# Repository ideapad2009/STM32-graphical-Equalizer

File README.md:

# STM32-graphical-Equalizer
## STM32F413CG real-time graphical Equalizer using Mems Microphone & DFSDM for Audio Acquisition, I2S & WM8731 codec

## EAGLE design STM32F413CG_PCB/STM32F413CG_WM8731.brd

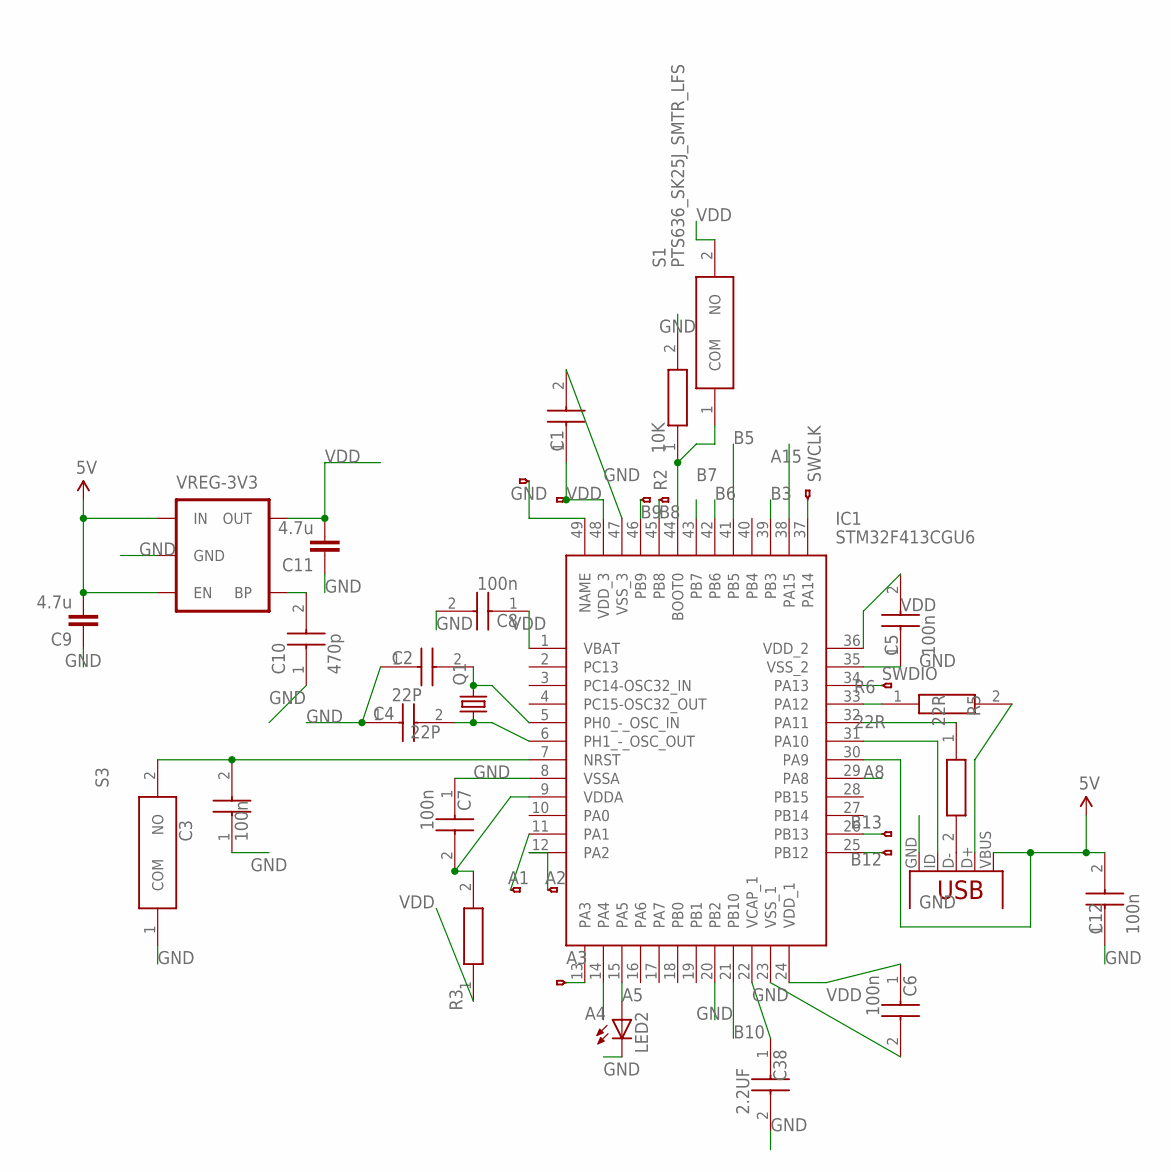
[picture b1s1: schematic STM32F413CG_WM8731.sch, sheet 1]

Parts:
C1: C0603C104M4RAC7411; CAPC1608X95N
C2, C4: 22P; CAPC1608X80N
C3, C5, C6, C7, C8, C12: 100n; CAPC1608X95N
C9, C11: 4.7u; C2.5-3
C10: 470p; CAPC1608X87N
C38: 2.2UF; CAPC2012X145N
IC1: STM32F413CGU6; QFN50P700X700X60-49N
JP1, JP2, JP3, JP4, JP5, JP6, JP7, JP8, JP9, JP10, JP11: HEADERHOLE-HEADERHOLE; 1X1-HEADER-HOLE
LED2: LED0603; LED-0603
Q1: CRYSTALHC49S; HC49/S
R2: 10K; RESC1005X40N
R3: CRCW040222R0FKED; RESC1005X40N
R5, R6: 22R; RESC1005X40N
S1, S3: PTS636_SK25J_SMTR_LFS; PTS636SK25JSMTRLFS
VREG-3V3: V_REG_LDOSMD; SOT23-5
X1: USB-MICROB-SMD

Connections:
5V: C9.2, C12.2, IC1.30 (PA9), VREG-3V3.1 (IN), VREG-3V3.3 (EN), X1.VBUS
A1: IC1.11 (PA1), JP8.1
A2: IC1.12 (PA2), JP9.1
A3: IC1.13 (PA3), JP10.1
A4: IC1.14 (PA4); also elsewhere on the board
A5: IC1.15 (PA5), LED2.A
A8: IC1.29 (PA8); also elsewhere on the board
A15: IC1.38 (PA15); also elsewhere on the board
B3: IC1.39 (PB3); also elsewhere on the board
B5: IC1.41 (PB5); also elsewhere on the board
B6: IC1.42 (PB6); also elsewhere on the board
B7: IC1.43 (PB7); also elsewhere on the board
B8: IC1.45 (PB8), JP5.1
B9: IC1.46 (PB9), JP11.1
B10: IC1.21 (PB10); also elsewhere on the board
B12: IC1.25 (PB12), JP7.1
B13: IC1.26 (PB13), JP6.1
GND: C1.2, C2.1, C3.1, C4.1, C5.1, C6.2, C7.1, C8.2, C9.1, C10.1, C11.1, C12.1, C38.2, IC1.8 (VSSA), IC1.20 (PB2), IC1.23 (VSS_1), IC1.35 (VSS_2), IC1.47 (VSS_3), IC1.49 (NAME), JP1.1, LED2.C, R2.2, S3.1 (COM), VREG-3V3.2 (GND), X1.GND; also elsewhere on the board
unnamed: C2.2, IC1.5 (PH0_-_OSC_IN), Q1.2
unnamed: C3.2, IC1.7 (NRST), S3.2 (NO)
unnamed: C10.2, VREG-3V3.4 (BP)
unnamed: C7.2, IC1.9 (VDDA), R3.2
unnamed: R5.2, X1.D-
unnamed: IC1.31 (PA10), X1.ID
unnamed: IC1.32 (PA11), R5.1
unnamed: R6.2, X1.D+
unnamed: IC1.33 (PA12), R6.1
unnamed: IC1.44 (BOOT0), R2.1, S1.1 (COM)
unnamed: C4.2, IC1.6 (PH1_-_OSC_OUT), Q1.1
unnamed: C38.1, IC1.22 (VCAP_1)
SWCLK: IC1.37 (PA14), JP2.1
SWDIO: IC1.34 (PA13), JP3.1
VDD: C1.1, C5.2, C6.1, C8.1, C11.2, IC1.1 (VBAT), IC1.24 (VDD_1), IC1.36 (VDD_2), IC1.48 (VDD_3), JP4.1, R3.1, S1.2 (NO), VREG-3V3.5 (OUT); also elsewhere on the board

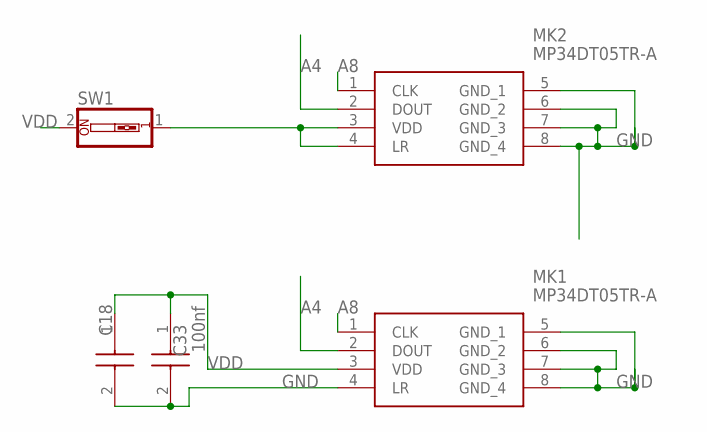
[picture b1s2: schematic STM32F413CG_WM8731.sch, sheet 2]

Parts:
C18: 1UF; CAPC1005X55N
C33: 100nf; CAPC1608X95N
MK1, MK2: MP34DT05TR-A; MP34DT05TRA
SW1: SW_DIP-1; EDG-01

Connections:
A4: MK1.2 (DOUT), MK2.2 (DOUT); also elsewhere on the board
A8: MK1.1 (CLK), MK2.1 (CLK); also elsewhere on the board
GND: C18.2 (C2), C33.2, MK1.4 (LR), MK1.5 (GND_1), MK1.6 (GND_2), MK1.7 (GND_3), MK1.8 (GND_4), MK2.5 (GND_1), MK2.6 (GND_2), MK2.7 (GND_3), MK2.8 (GND_4); also elsewhere on the board
unnamed: MK2.3 (VDD), MK2.4 (LR), SW1.1
VDD: C18.1 (C1), C33.1, MK1.3 (VDD), SW1.2; also elsewhere on the board

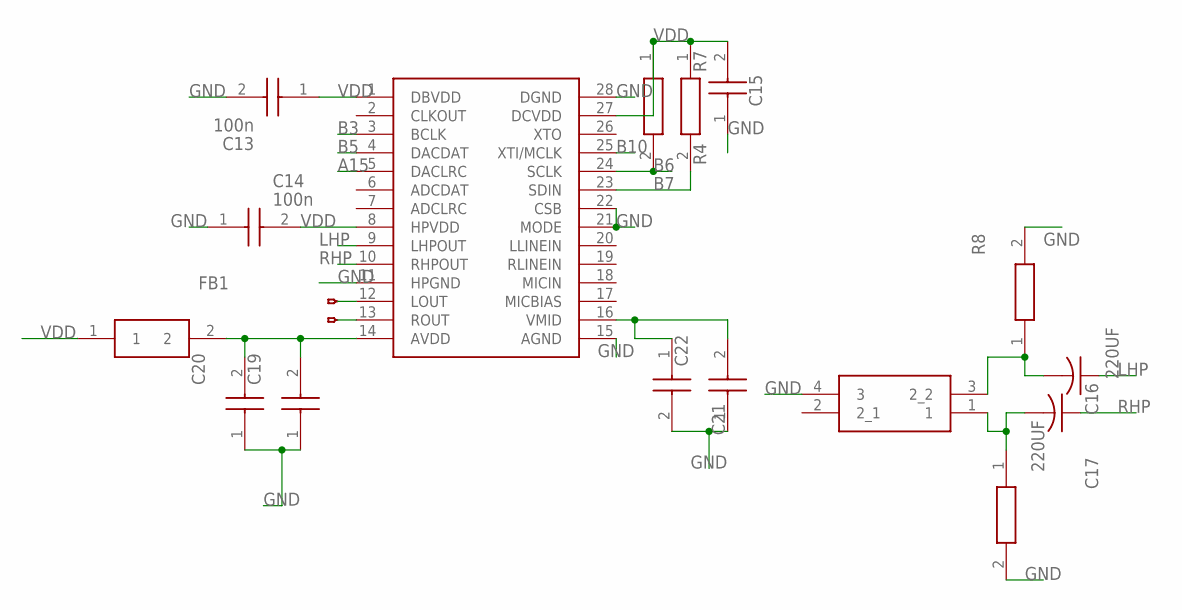
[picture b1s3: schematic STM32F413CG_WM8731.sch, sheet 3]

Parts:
C13, C14: 100n; CAPC1608X95N
C15, C19, C22: C0603C104M4RAC7411; CAPC1608X95N
C16, C17: 220UF; C025-024X044
C20: CL21A106KAYNNNE_10UF; CAPC2012X145N
C21: CL21A106KAYNNNE; CAPC2012X145N
FB1: BLM18BD252SN1D; BEADC1608X95N
IC2: WM8731SEDS_RV; SOP65P780X200-28N
J2: 1503_02; 150302
JP12, JP13: HEADERHOLE-HEADERHOLE; 1X1-HEADER-HOLE
R4, R7, R8, R9: CR0603-JW-472ELF; RESC1608X55N

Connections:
A15: IC2.5 (DACLRC); also elsewhere on the board
B3: IC2.3 (BCLK); also elsewhere on the board
B5: IC2.4 (DACDAT); also elsewhere on the board
B6: IC2.24 (SCLK), R4.2; also elsewhere on the board
B7: IC2.23 (SDIN), R7.2; also elsewhere on the board
B10: IC2.25 (XTI/MCLK); also elsewhere on the board
GND: C13.2, C14.1, C15.1, C19.1, C20.1, C21.2, C22.1, IC2.11 (HPGND), IC2.15 (AGND), IC2.21 (MODE), IC2.22 (CSB), IC2.28 (DGND), J2.4 (3), R8.2, R9.2; also elsewhere on the board
LHP: C16.1, IC2.9 (LHPOUT)
unnamed: C16.2, J2.3 (2_2), R8.1
unnamed: C19.2, C20.2, FB1.2, IC2.14 (AVDD)
unnamed: C21.1, C22.2, IC2.16 (VMID)
unnamed: IC2.12 (LOUT), JP13.1
unnamed: IC2.13 (ROUT), JP12.1
unnamed: C17.2, J2.1, R9.1
RHP: C17.1, IC2.10 (RHPOUT)
VDD: C13.1, C14.2, C15.2, FB1.1, IC2.1 (DBVDD), IC2.8 (HPVDD), IC2.27 (DCVDD), R4.1, R7.1; also elsewhere on the board

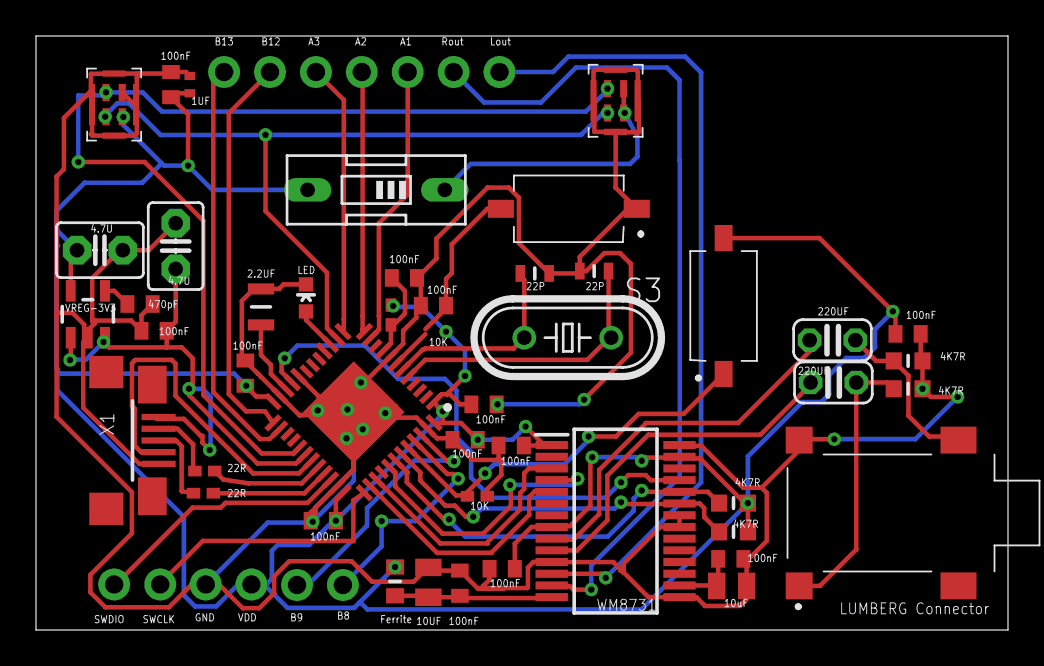
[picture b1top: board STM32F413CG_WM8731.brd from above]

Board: 2 copper layers, 54.0 x 33.0 mm, 58 parts (0 on the bottom side), 42 nets.

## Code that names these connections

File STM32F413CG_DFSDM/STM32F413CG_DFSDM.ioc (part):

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Mcu.Name=STM32F413C(G-H)Ux
Mcu.Package=UFQFPN48
Mcu.UserName=STM32F413CGUx
PA13.Mode=Serial_Wire
PA13.Signal=SYS_JTMS-SWDIO
PA14.Mode=Serial_Wire
PA14.Signal=SYS_JTCK-SWCLK
PA4.Signal=COMP_DAC1_group
PA5.GPIOParameters=GPIO_Speed,PinState
PA5.GPIO_Speed=GPIO_SPEED_FREQ_HIGH
PA5.PinState=GPIO_PIN_SET
PA5.Signal=GPIO_Output
PA8.Signal=S_CKOUTDFSDM1
PB12.Signal=S_DATAIN1DFSDM1
PB3.Signal=I2S3_CK
PB6.Mode=I2C
PB6.Signal=I2C1_SCL
PB7.Mode=I2C
PB7.Signal=I2C1_SDA
PB8.Mode=Asynchronous
PB8.Signal=UART5_RX
PB9.Mode=Asynchronous
PB9.Signal=UART5_TX
PH0\ -\ OSC_IN.Mode=HSE-External-Oscillator
PH0\ -\ OSC_IN.Signal=RCC_OSC_IN
PH1\ -\ OSC_OUT.Mode=HSE-External-Oscillator
PH1\ -\ OSC_OUT.Signal=RCC_OSC_OUT
RCC.HSE_VALUE=8000000
RCC.SYSCLKFreq_VALUE=80000000
RCC.SYSCLKSource=RCC_SYSCLKSOURCE_PLLCLK
board=custom

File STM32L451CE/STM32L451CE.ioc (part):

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Mcu.Name=STM32L451C(C-E)Ux
Mcu.Package=UFQFPN48
Mcu.UserName=STM32L451CEUx
PA10.Mode=Asynchronous
PA10.Signal=USART1_RX
PA13\ (JTMS/SWDIO).Mode=Serial_Wire
PA13\ (JTMS/SWDIO).Signal=SYS_JTMS-SWDIO
PA14\ (JTCK/SWCLK).Mode=Serial_Wire
PA14\ (JTCK/SWCLK).Signal=SYS_JTCK-SWCLK
PA4.Signal=COMP_DAC11_group
PA5.Signal=S_CKOUTDFSDM1
PA7.Signal=S_DATAIN0DFSDM1
PA8.GPIOParameters=PinState
PA8.PinState=GPIO_PIN_SET
PA8.Signal=GPIO_Output
PA9.Mode=Asynchronous
PA9.Signal=USART1_TX
PB6.Mode=I2C
PB6.Signal=I2C1_SCL
PB7.Mode=I2C
PB7.Signal=I2C1_SDA
PB8.Signal=GPIO_Output
RCC.HSE_VALUE=8000000
RCC.SYSCLKFreq_VALUE=72000000
RCC.SYSCLKSource=RCC_SYSCLKSOURCE_PLLCLK
board=custom

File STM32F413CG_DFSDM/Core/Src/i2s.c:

/**
  ******************************************************************************
  * File Name          : I2S.c
  * Description        : This file provides code for the configuration
  *                      of the I2S instances.
  ******************************************************************************
  * @attention
  *
  * <h2><center>&copy; Copyright (c) 2020 STMicroelectronics.
  * All rights reserved.</center></h2>
  *
  * This software component is licensed by ST under BSD 3-Clause license,
  * the "License"; You may not use this file except in compliance with the
  * License. You may obtain a copy of the License at:
  *                        opensource.org/licenses/BSD-3-Clause
  *
  ******************************************************************************
  */

/* Includes ------------------------------------------------------------------*/
#include "i2s.h"

/* USER CODE BEGIN 0 */

/* USER CODE END 0 */

I2S_HandleTypeDef hi2s3;
DMA_HandleTypeDef hdma_spi3_tx;

/* I2S3 init function */
void MX_I2S3_Init(void)
{

  hi2s3.Instance = SPI3;
  hi2s3.Init.Mode = I2S_MODE_MASTER_TX;
  hi2s3.Init.Standard = I2S_STANDARD_PHILIPS;
  hi2s3.Init.DataFormat = I2S_DATAFORMAT_24B;
  hi2s3.Init.MCLKOutput = I2S_MCLKOUTPUT_ENABLE;
  hi2s3.Init.AudioFreq = I2S_AUDIOFREQ_48K;
  hi2s3.Init.CPOL = I2S_CPOL_LOW;
  hi2s3.Init.ClockSource = I2S_CLOCK_PLL;
  hi2s3.Init.FullDuplexMode = I2S_FULLDUPLEXMODE_DISABLE;
  if (HAL_I2S_Init(&hi2s3) != HAL_OK)
  {
    Error_Handler();
  }

}

void HAL_I2S_MspInit(I2S_HandleTypeDef* i2sHandle)
{

  GPIO_InitTypeDef GPIO_InitStruct = {0};
  if(i2sHandle->Instance==SPI3)
  {
  /* USER CODE BEGIN SPI3_MspInit 0 */

  /* USER CODE END SPI3_MspInit 0 */
    /* I2S3 clock enable */
    __HAL_RCC_SPI3_CLK_ENABLE();

    __HAL_RCC_GPIOB_CLK_ENABLE();
    __HAL_RCC_GPIOA_CLK_ENABLE();
    /**I2S3 GPIO Configuration
    PB10     ------> I2S3_MCK
    PA15     ------> I2S3_WS
    PB3     ------> I2S3_CK
    PB5     ------> I2S3_SD
    */
    GPIO_InitStruct.Pin = GPIO_PIN_10|GPIO_PIN_3|GPIO_PIN_5;
    GPIO_InitStruct.Mode = GPIO_MODE_AF_PP;
    GPIO_InitStruct.Pull = GPIO_NOPULL;
    GPIO_InitStruct.Speed = GPIO_SPEED_FREQ_LOW;
    GPIO_InitStruct.Alternate = GPIO_AF6_SPI3;
    HAL_GPIO_Init(GPIOB, &GPIO_InitStruct);

    GPIO_InitStruct.Pin = GPIO_PIN_15;
    GPIO_InitStruct.Mode = GPIO_MODE_AF_PP;
    GPIO_InitStruct.Pull = GPIO_NOPULL;
    GPIO_InitStruct.Speed = GPIO_SPEED_FREQ_LOW;
    GPIO_InitStruct.Alternate = GPIO_AF6_SPI3;
    HAL_GPIO_Init(GPIOA, &GPIO_InitStruct);

    /* I2S3 DMA Init */
    /* SPI3_TX Init */
    hdma_spi3_tx.Instance = DMA1_Stream7;
    hdma_spi3_tx.Init.Channel = DMA_CHANNEL_0;
    hdma_spi3_tx.Init.Direction = DMA_MEMORY_TO_PERIPH;
    hdma_spi3_tx.Init.PeriphInc = DMA_PINC_DISABLE;
    hdma_spi3_tx.Init.MemInc = DMA_MINC_ENABLE;
    hdma_spi3_tx.Init.PeriphDataAlignment = DMA_PDATAALIGN_HALFWORD;
    hdma_spi3_tx.Init.MemDataAlignment = DMA_MDATAALIGN_HALFWORD;
    hdma_spi3_tx.Init.Mode = DMA_CIRCULAR;
    hdma_spi3_tx.Init.Priority = DMA_PRIORITY_HIGH;
    hdma_spi3_tx.Init.FIFOMode = DMA_FIFOMODE_DISABLE;
    if (HAL_DMA_Init(&hdma_spi3_tx) != HAL_OK)
    {
      Error_Handler();
    }

    __HAL_LINKDMA(i2sHandle,hdmatx,hdma_spi3_tx);

  /* USER CODE BEGIN SPI3_MspInit 1 */

  /* USER CODE END SPI3_MspInit 1 */
  }
}

void HAL_I2S_MspDeInit(I2S_HandleTypeDef* i2sHandle)
{

  if(i2sHandle->Instance==SPI3)
  {
  /* USER CODE BEGIN SPI3_MspDeInit 0 */

  /* USER CODE END SPI3_MspDeInit 0 */
    /* Peripheral clock disable */
    __HAL_RCC_SPI3_CLK_DISABLE();

    /**I2S3 GPIO Configuration
    PB10     ------> I2S3_MCK
    PA15     ------> I2S3_WS
    PB3     ------> I2S3_CK
    PB5     ------> I2S3_SD
    */
    HAL_GPIO_DeInit(GPIOB, GPIO_PIN_10|GPIO_PIN_3|GPIO_PIN_5);

    HAL_GPIO_DeInit(GPIOA, GPIO_PIN_15);

    /* I2S3 DMA DeInit */
    HAL_DMA_DeInit(i2sHandle->hdmatx);
  /* USER CODE BEGIN SPI3_MspDeInit 1 */

  /* USER CODE END SPI3_MspDeInit 1 */
  }
}

/* USER CODE BEGIN 1 */

/* USER CODE END 1 */

/************************ (C) COPYRIGHT STMicroelectronics *****END OF FILE****/

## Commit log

2020-04-24 STM32F413CG project
2020-04-24 clear repo
2020-04-25 added graphical equalizer libraray
2020-05-01 added CMSIS
2020-06-11 stable release
2020-06-12 first commit test
2020-06-12 continue master
2020-06-12 changed DFSDM MIC polarity
2020-06-12 testtt
2020-06-12 changed sampling frequency of DFSDM and I2S to 44642
2020-06-12 fixed DFDDM MUX to change sampling frequency of DFSDM and I2S to 44642
2020-07-18 Successfully test DAC with Timer6
2020-07-25 test to DAC_output branch
2020-07-25 successfully added DAC_Output with Timer6
2020-07-25 added not staged files to DAC_output branch
2020-07-25 Revert "Successfully test DAC with Timer6"
    This reverts commit ac6be118d610ab295486c276112780f5274638ee.
2020-07-25 removed CMSIS source code files
2020-08-02 added CMSIS iir Filters to DAC
2020-08-02 added CMSIS iir Filters to DAC_2
2020-08-02 optimizing unused code
2020-08-03 added binaries
2020-08-03 added PCB files
2020-08-15 added some photo, changed shift by 8 before converting to float
2020-08-15 changes due to STMCUBEMXIDE update
2020-08-15 changed HSI clock from 80MHZ to 64MHZ and changes due to STMCUBEIDE update
2020-08-15 finally STM32CubeMx version 6.0.1 changes update
2020-08-15 changes path of images
2020-08-24 done some cleanup
2020-08-24 Did some cleanup and upgrading the STM32CubeIDE chanegd some files
2020-08-24 upgrading STM32CUBEIDE and cleanup
2020-08-24 added changes to body_DAC_DFSDM.h to be similar to that in DAC_output branch
2020-08-24 added STM32L451CE files
2020-08-25 changed Sinc order in STM32L451CE
2020-08-25 added STM32L451CE Project file
